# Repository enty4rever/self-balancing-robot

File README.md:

# self-balancing-robot
Two-wheeled self-balancing robot using ESP32, MPU6050 IMU and cascade PID control. Built with PlatformIO.

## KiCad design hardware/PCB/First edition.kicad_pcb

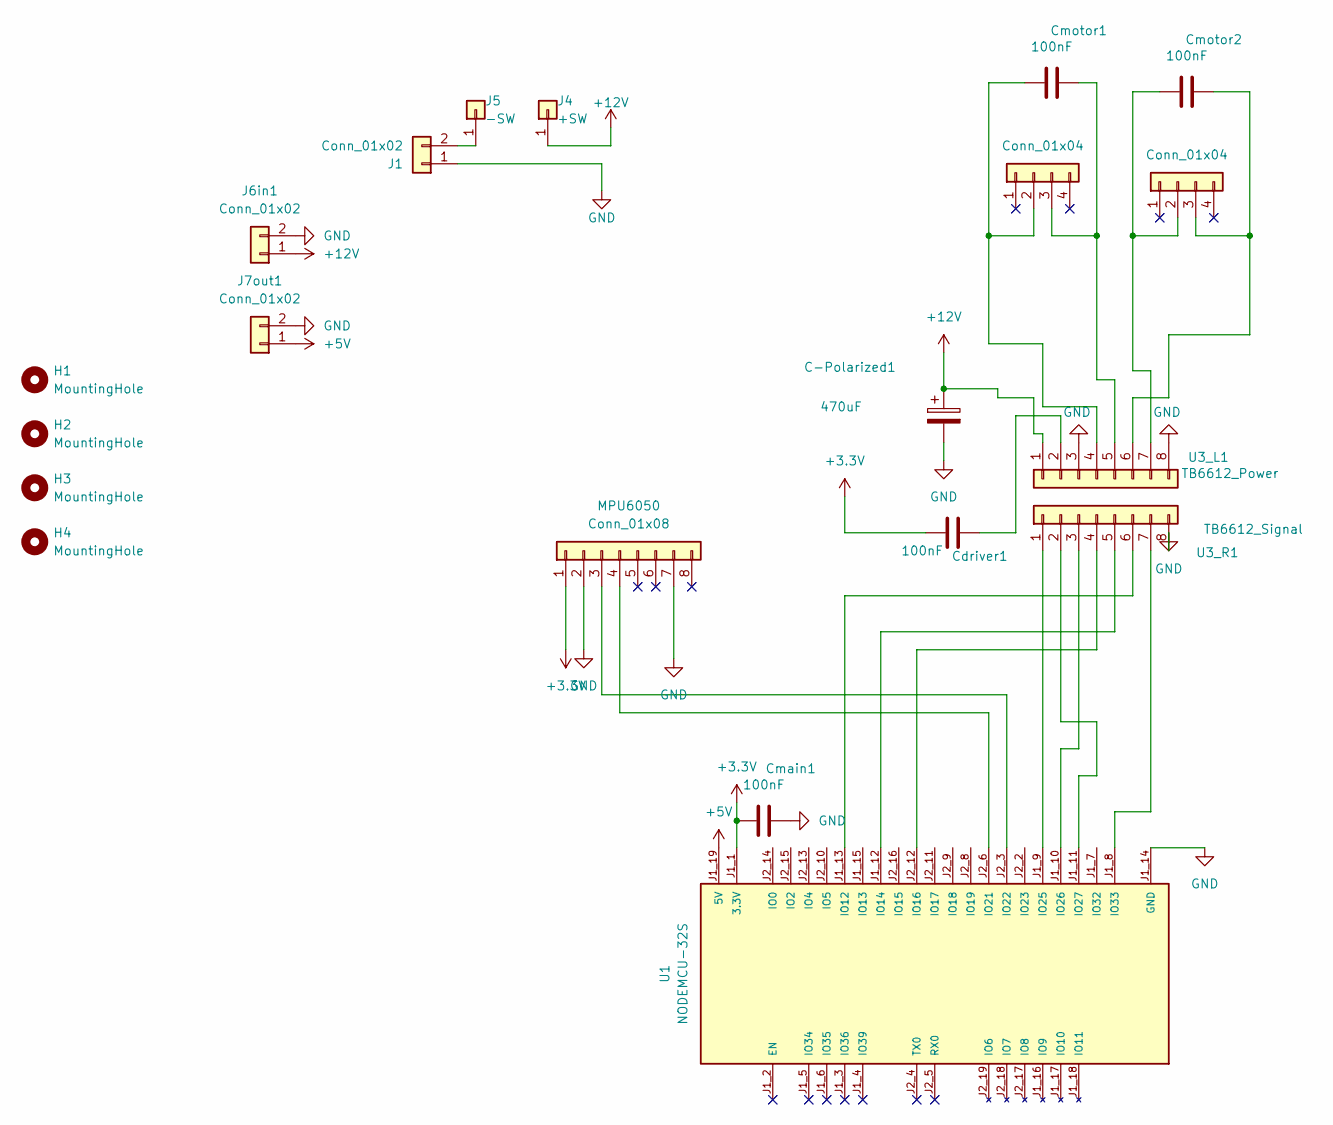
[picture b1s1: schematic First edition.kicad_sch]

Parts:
C-Polarized1: 470uF; CP_Radial_D8.0mm_P5.00mm
Cdriver1: 100nF; C_0805_2012Metric
Cmain1: 100nF; C_0805_2012Metric
Cmotor1, Cmotor2: 100nF; C_0805_2012Metric
H1, H2, H3, H4: MountingHole; MountingHole_3.2mm_M3_DIN965_Pad
J1, J6in1, J7out1: Conn_01x02; TerminalBlock_Phoenix_MKDS-1,5-2-5.08_1x02_P5.08mm_Horizont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
J2, J3: Conn_01x04; JST_XH_B4B-XH-AM_1x04_P2.50mm_Vertical
J4: +SW; TestPoint_Pad_D2.5mm
J5: -SW; TestPoint_Pad_D2.5mm
MPU6050: Conn_01x08; PinHeader_1x08_P2.54mm_Vertical
U1: NODEMCU-32S; MODULE_NODEMCU-32S; PARTREV V1
U3_L1: TB6612_Power; PinHeader_1x08_P2.54mm_Vertical
U3_R1: TB6612_Signal; PinHeader_1x08_P2.54mm_Vertical

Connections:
+3.3V: Cdriver1.1, Cmain1.1, MPU6050.1, U1.J1_1 (3.3V)
+5V: J7out1.1, U1.J1_19 (5V)
+12V: C-Polarized1.1, J4.1 (Pin_1_1), J6in1.1, U3_L1.1; also elsewhere on the board
GND: C-Polarized1.2, Cmain1.2, J1.1, J6in1.2, J7out1.2, MPU6050.2, MPU6050.7, U1.J1_14 (GND), U1.J2_1 (GND), U1.J2_7 (GND), U3_L1.3, U3_L1.8, U3_R1.8
unnamed 4: J1.2, J5.1 (Pin_1_1); also elsewhere on the board
unnamed: Cmotor1.1, J2.2, U3_L1.4
unnamed: Cmotor1.2, J2.3, U3_L1.5
unnamed: Cmotor2.1, J3.2, U3_L1.7
unnamed: Cmotor2.2, J3.3, U3_L1.6
unnamed: MPU6050.3, U1.J2_3 (IO22)
unnamed: MPU6050.4, U1.J2_6 (IO21)
unnamed: U1.J1_13 (IO12), U3_R1.6
unnamed: U1.J1_12 (IO14), U3_R1.5
unnamed: U1.J2_12 (IO16), U3_R1.4
unnamed: U1.J1_9 (IO25), U3_R1.1
unnamed: U1.J1_10 (IO26), U3_R1.3
unnamed: U1.J1_11 (IO27), U3_R1.2
unnamed: U1.J1_8 (IO33), U3_R1.7
unnamed: Cdriver1.2, U3_L1.2

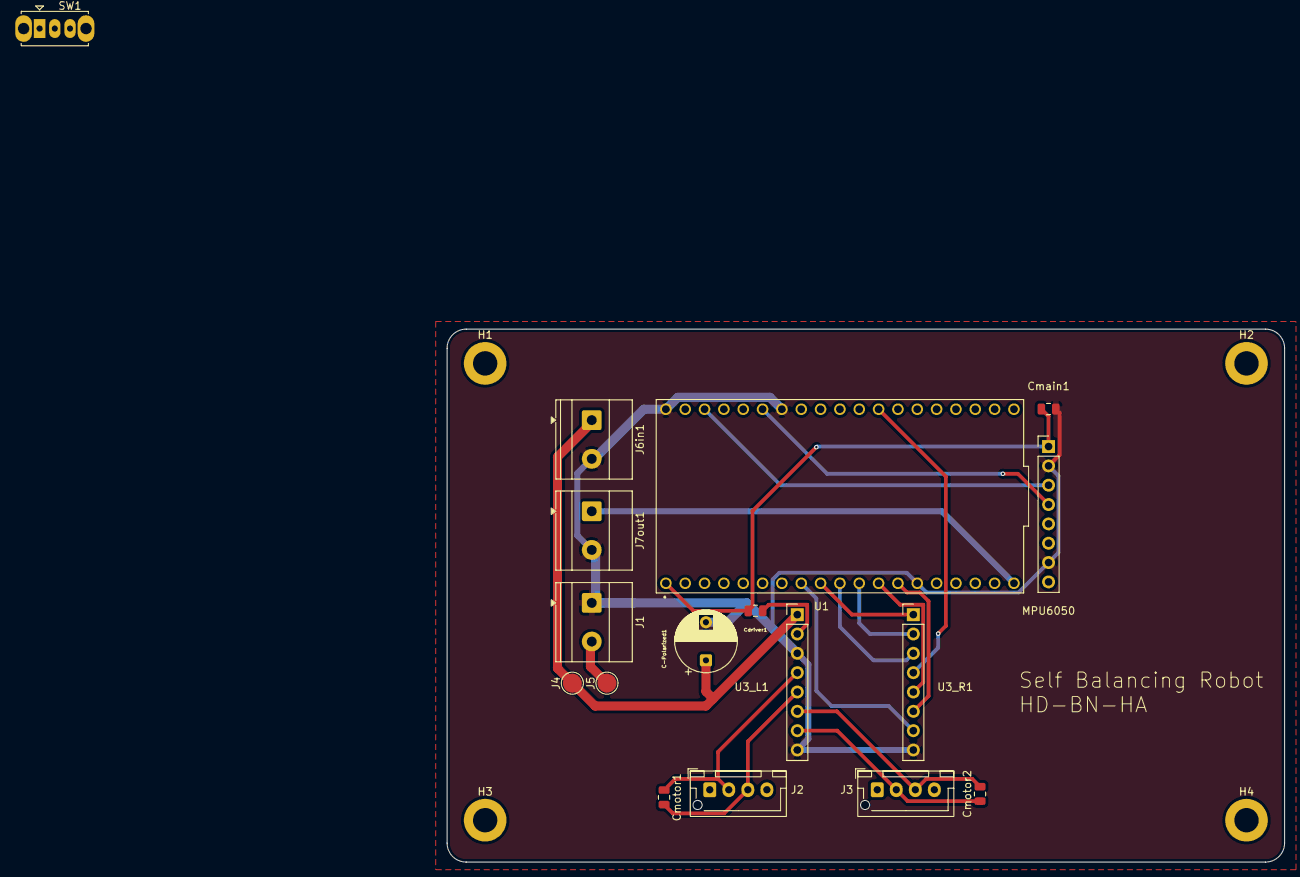
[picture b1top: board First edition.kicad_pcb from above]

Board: 2 copper layers, 110.0 x 70.0 mm, 21 parts (0 on the bottom side), 19 nets.

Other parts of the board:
SW1: SW_SPDT; SW_Slide_SPDT_Straight_CK_OS102011MS2Q

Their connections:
+12V: SW1.1 (A); also elsewhere on the board
unnamed 4: SW1.2 (B); also elsewhere on the board

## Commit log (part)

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2026-06-17 bill of materials
2026-06-20 test sketch 1: I2C test
2026-06-20 test sketch 1: change file and folder name
2026-06-20 test sketch 2: angle read test
2026-06-20 test sketch 2: fix bug
2026-06-21 test sketch 3: motor test
2026-06-21 test sketch 3: fix bug
2026-06-21 test sketch 3: fix bug + direct reveral test
